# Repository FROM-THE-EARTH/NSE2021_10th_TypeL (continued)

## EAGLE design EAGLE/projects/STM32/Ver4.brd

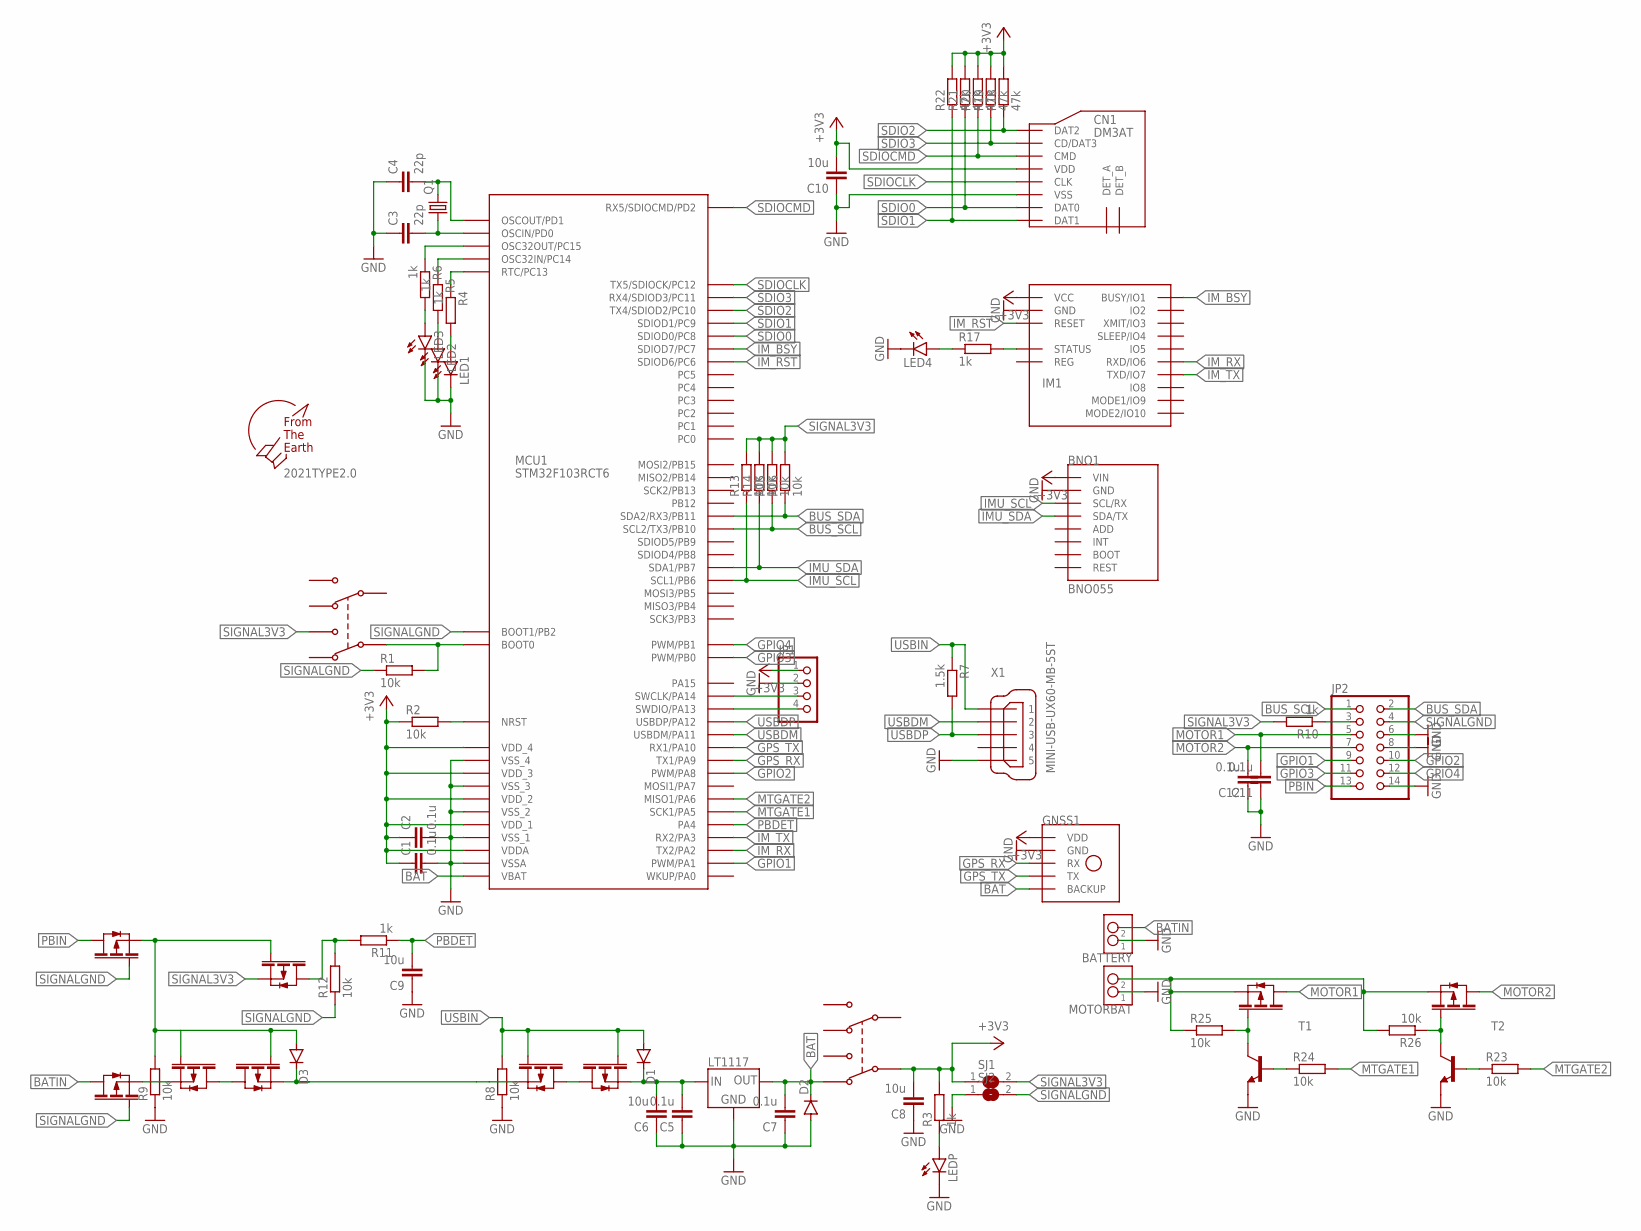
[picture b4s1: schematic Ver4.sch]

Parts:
2021TYPE2.0: F.T.E.LOGO; LOGO
BATTERY: S2B-XH-A
BNO1: BNO055
C1, C2, C5, C7, C11, C12: 0.1u; C1608
C3, C4: 22p; C1608
C6, C8, C9, C10: 10u; C1608
CN1: DM3AT
D1, D2, D3: DIODE-SOD123; SOD123
FET1, FET2, FET3, FET4, FET5, FET6, FET7, FET8, FET9: PCH; SOT-23
GNSS1: GYSFDMAXB
IC1: LT1117-3.3; SOT-223
IM1: IM920C
JP1: PINHD-1X4/90; 1X04/90
JP2: PINHD-2X7; 2X07
LED1, LED2, LED3, LED4: LEDSML0805; SML0805
LEDP: LEDSML0805; SML0805
MCU1: STM32F103RCT6; LQFP64
MOTORBAT: S2B-XH-A
Q1: CRYSTALHC49S; HC49/S
R1, R2, R8, R9, R12, R13, R14, R15, R16, R23, R24, R25, R26: 10k; R0805
R3, R4, R5, R6, R10, R11, R17: 1k; R0805
R7: 1.5k; R0805
R18, R19, R20, R21, R22: 47k; R0805
SJ1, SJ2: SJ
T1, T2: -NPN-SOT23-EBC; SOT23-EBC
U$1, U$2: MSS22D18
X1: MINI-USB-UX60-MB-5ST; UX60-MB-5ST

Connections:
+3V3: BNO1.P1 (VIN), C1.1, C2.1, C8.2, C10.2, CN1.VDD, GNSS1.P$16 (VDD), IM1.$P17 (VCC), JP1.1, MCU1.P$13 (VDDA), MCU1.P$19 (VDD_4), MCU1.P$32 (VDD_1), MCU1.P$48 (VDD_2), MCU1.P$64 (VDD_3), R2.1, R3.2, R18.2, R19.2, R20.2, R21.2, R22.2, SJ1.1, U$2.P$4
BAT: C7.2, D2.C, GNSS1.P$14 (BACKUP), IC1.1 (OUT), IC1.2 (OUT), MCU1.P$1 (VBAT), U$2.P$3
BATIN: BATTERY.P$2 (2), FET5.P$3
BAT_FET_FET1: FET3.P$2, FET5.P$2
BAT_FET_FET2: FET3.P$3, FET4.P$3
BOOT0: MCU1.P$60 (BOOT0), R1.2, U$1.P$4
BUS_3V3: JP2.3, R10.1
BUS_SCL: JP2.1, MCU1.P$29 (SCL2/TX3/PB10), R15.1
BUS_SDA: JP2.2, MCU1.P$30 (SDA2/RX3/PB11), R16.1
DIODE_FET: D3.C, FET1.P$2, FET4.P$2
FET_REG: C5.2, C6.2, D1.C, FET2.P$2, IC1.3 (IN)
GND: BATTERY.P$1 (1), BNO1.P2 (GND), C1.2, C2.2, C3.1, C4.1, C5.1, C6.1, C7.1, C8.1, C9.1, C10.1, C11.1, C12.1, CN1.VSS, D2.A, GNSS1.P$1 (GND), GNSS1.P$2 (GND), GNSS1.P$7 (GND), GNSS1.P$10 (GND), GNSS1.P$12 (GND), GNSS1.P$19 (GND), GNSS1.P$20 (GND), IC1.4 (GND), IM1.$P18 (GND), JP1.2, JP2.6, JP2.8, JP2.14, LED1.C, LED2.C, LED3.C, LED4.C, LEDP.C, MCU1.P$12 (VSSA), MCU1.P$18 (VSS_4), MCU1.P$31 (VSS_1), MCU1.P$47 (VSS_2), MCU1.P$63 (VSS_3), MOTORBAT.P$1 (1), R8.1, R9.1, SJ2.1, T2.E, X1.5
GPIO1: JP2.9, MCU1.P$15 (PWM/PA1)
GPIO2: JP2.10, MCU1.P$41 (PWM/PA8)
GPIO3: JP2.11, MCU1.P$26 (PWM/PB0)
GPIO4: JP2.12, MCU1.P$27 (PWM/PB1)
GPS_RX: GNSS1.P$3 (RX), MCU1.P$42 (TX1/PA9)
GPS_TX: GNSS1.P$5 (TX), MCU1.P$43 (RX1/PA10)
IMU_SCL: BNO1.P3 (SCL/RX), MCU1.P$58 (SCL1/PB6), R13.1
IMU_SDA: BNO1.P4 (SDA/TX), MCU1.P$59 (SDA1/PB7), R14.1
IM_BSY: IM1.$P1 (BUSY/IO1), MCU1.P$38 (SDIOD7/PC7)
IM_RST: IM1.$P19 (RESET), MCU1.P$37 (SDIOD6/PC6)
IM_RX: IM1.$P6 (RXD/IO6), MCU1.P$16 (TX2/PA2)
IM_ST_R: IM1.$P15 (STATUS), R17.2
IM_TX: IM1.$P7 (TXD/IO7), MCU1.P$17 (RX2/PA3)
MOTOR1: C11.2, FET9.P$3, JP2.5
MOTOR2: C12.2, FET8.P$3, JP2.7
MTBATIN: FET8.P$2, FET9.P$2, MOTORBAT.P$2 (2), R25.1, R26.2
MTGATE1: MCU1.P$21 (SCK1/PA5), R24.2
MTGATE2: MCU1.P$22 (MISO1/PA6), R23.2
NRST: MCU1.P$7 (NRST), R2.2
OSCIN: C3.2, MCU1.P$5 (OSCIN/PD0), Q1.1
OSCOUT: C4.2, MCU1.P$6 (OSCOUT/PD1), Q1.2
PBDET: C9.2, MCU1.P$20 (PA4), R11.1
PBDET_FET_R: FET7.P$3, R11.2, R12.2
PBIN: FET6.P$3, JP2.13
PB_FET_DIODE: D3.A, FET3.P$1, FET4.P$1, FET6.P$2, FET7.P$1, R9.2
PC13_R: MCU1.P$2 (RTC/PC13), R4.1
PC14_R: MCU1.P$3 (OSC32IN/PC14), R5.1
PC15_R: MCU1.P$4 (OSC32OUT/PC15), R6.1
R_LED1: LED1.A, R4.2
R_LED2: LED2.A, R5.2
R_LED3: LED3.A, R6.2
R_LED4: LED4.A, R17.1
R_LEDP: LEDP.A, R3.1
R_T1: FET9.P$1, R25.2, T1.C, T1.E
R_T2: FET8.P$1, R26.1, T2.C
SDIO0: CN1.DAT0, MCU1.P$39 (SDIOD0/PC8), R21.1
SDIO1: CN1.DAT1, MCU1.P$40 (SDIOD1/PC9), R22.1
SDIO2: CN1.DAT2, MCU1.P$51 (TX4/SDIOD2/PC10), R18.1
SDIO3: CN1.CD/DAT3, MCU1.P$52 (RX4/SDIOD3/PC11), R19.1
SDIOCLK: CN1.CLK, MCU1.P$53 (TX5/SDIOCK/PC12)
SDIOCMD: CN1.CMD, MCU1.P$54 (RX5/SDIOCMD/PD2), R20.1
SIGNAL3V3: FET7.P$2, R10.2, R13.2, R14.2, R15.2, R16.2, SJ1.2, U$1.P$5
SIGNALGND: FET5.P$1, FET6.P$1, JP2.4, MCU1.P$28 (BOOT1/PB2), R1.1, R12.1, SJ2.2
SWCLK: JP1.3, MCU1.P$49 (SWCLK/PA14)
SWDIO: JP1.4, MCU1.P$46 (SWDIO/PA13)
T1_BASE: R24.1, T1.B
T2_BASE: R23.1, T2.B
USBDM: MCU1.P$44 (USBDM/PA11), X1.2
USBDP: MCU1.P$45 (USBDP/PA12), R7.2, X1.3
USBIN: D1.A, FET1.P$1, FET2.P$1, R7.1, R8.2, X1.1
USB_FET_FET: FET1.P$3, FET2.P$3

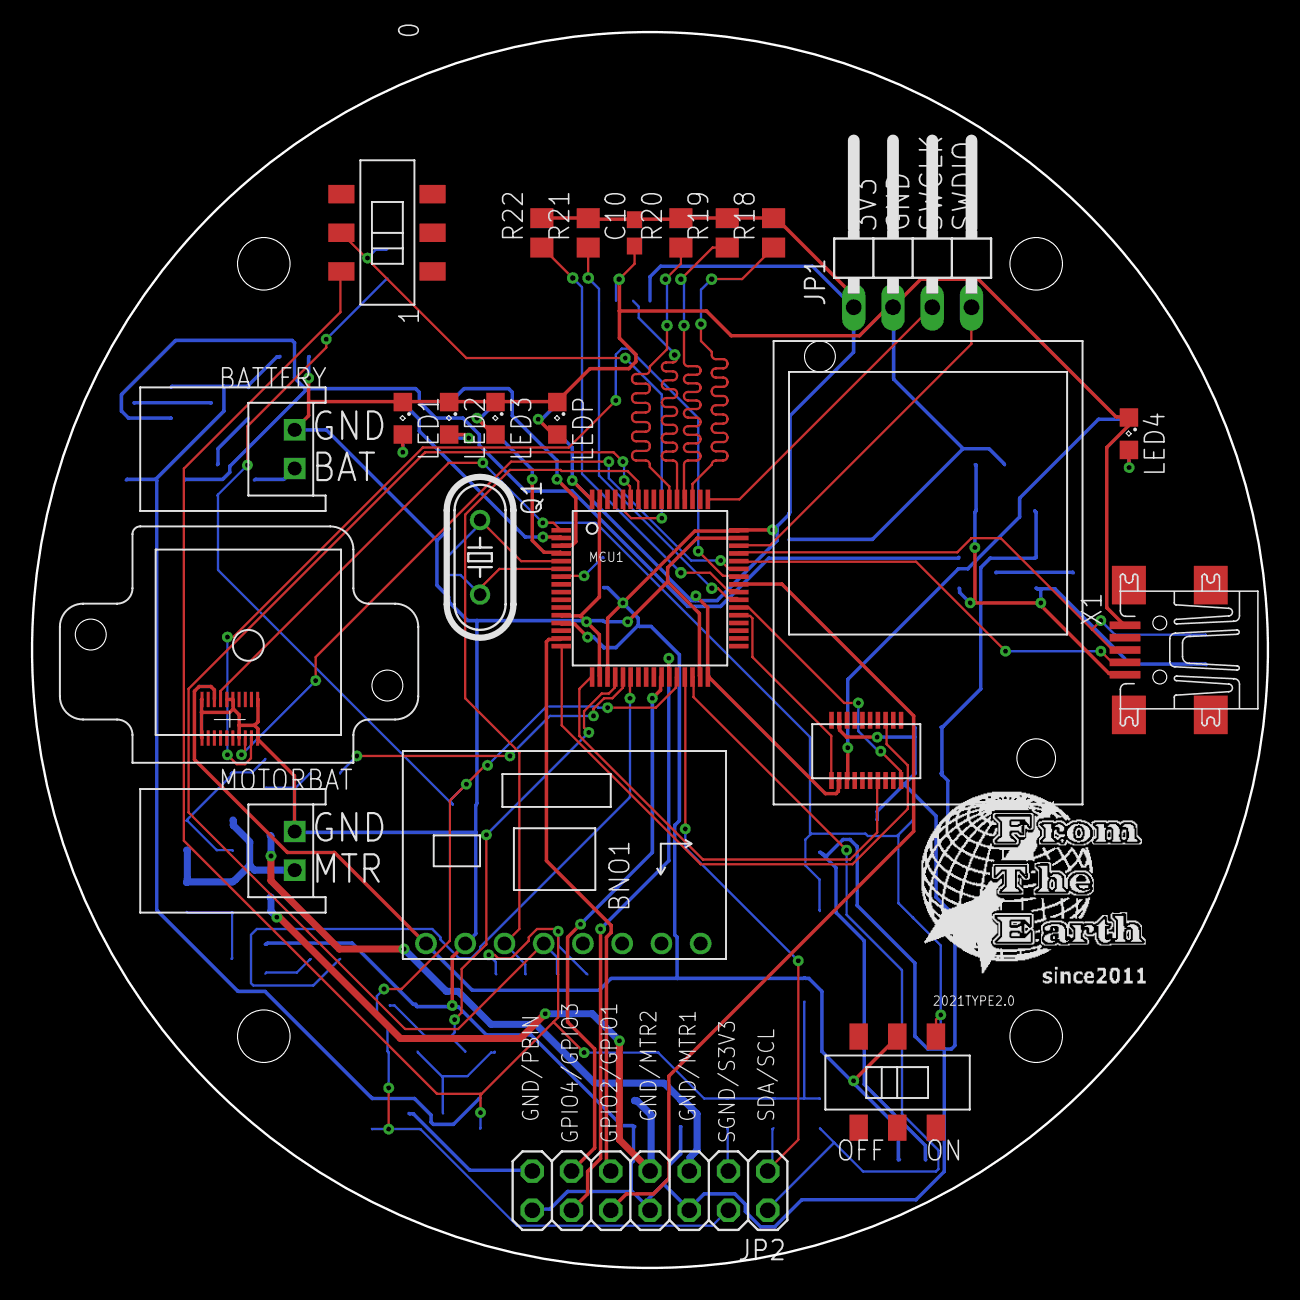
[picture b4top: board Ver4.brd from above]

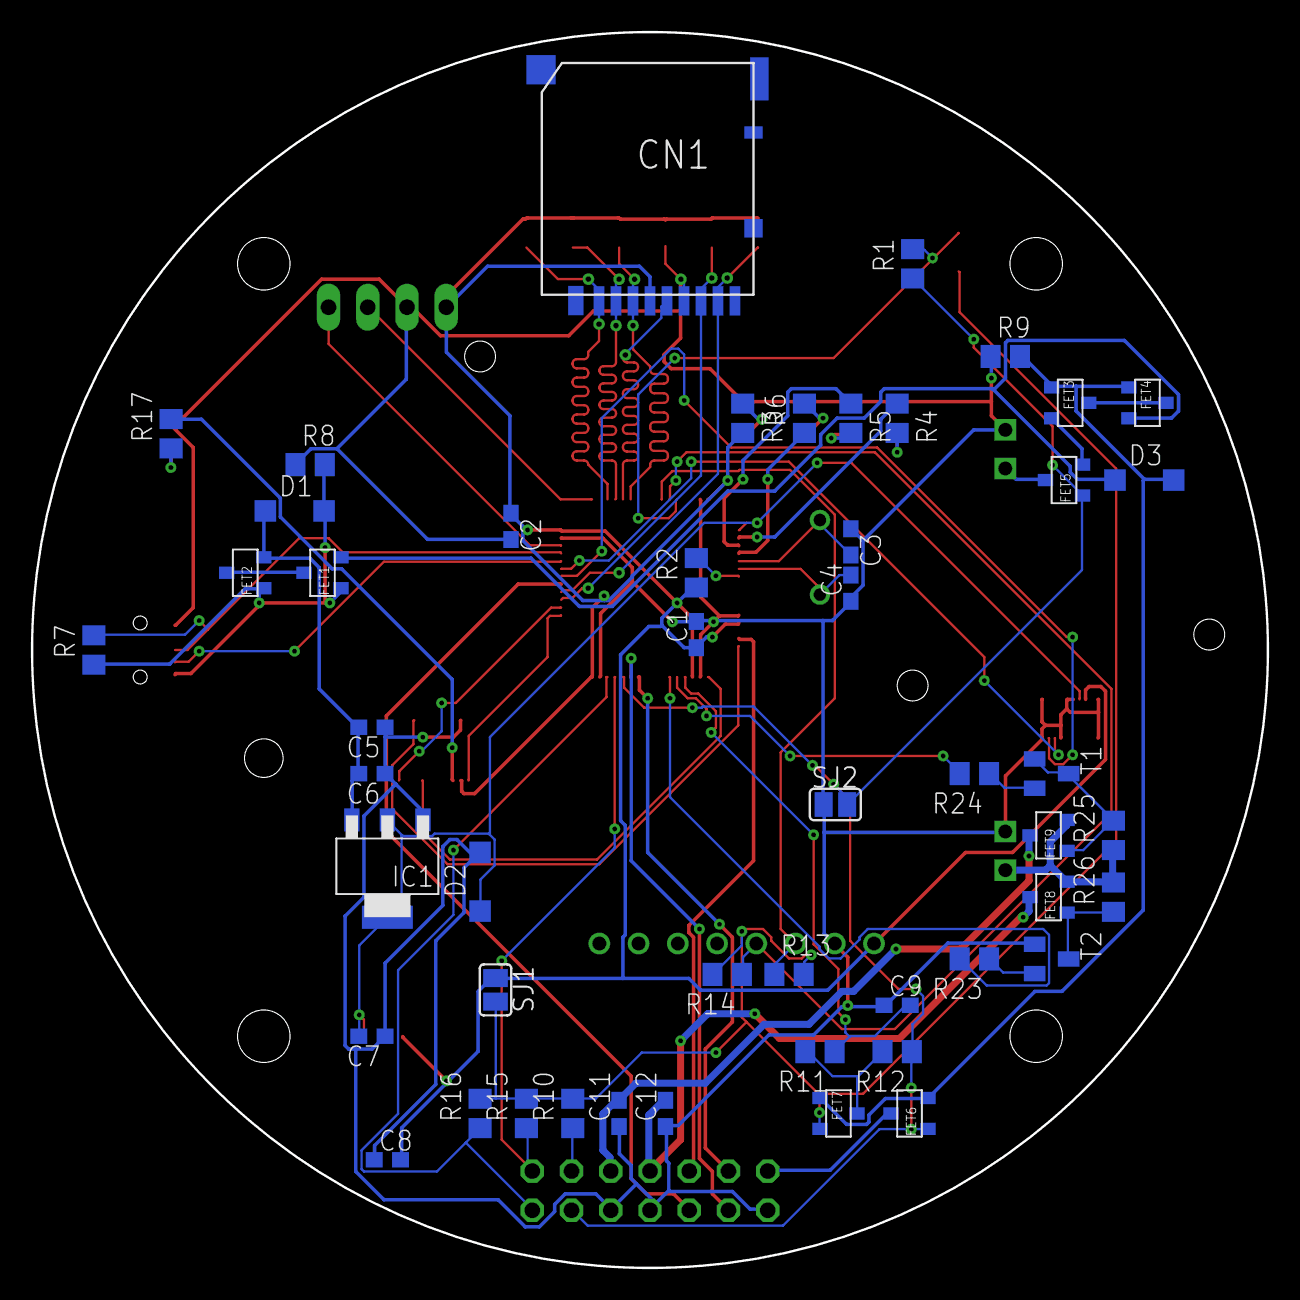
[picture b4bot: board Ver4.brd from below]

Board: 2 copper layers, 80.0 x 80.0 mm, 74 parts (50 on the bottom side), 63 nets.

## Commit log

2021-05-17 EAGLEデータ
